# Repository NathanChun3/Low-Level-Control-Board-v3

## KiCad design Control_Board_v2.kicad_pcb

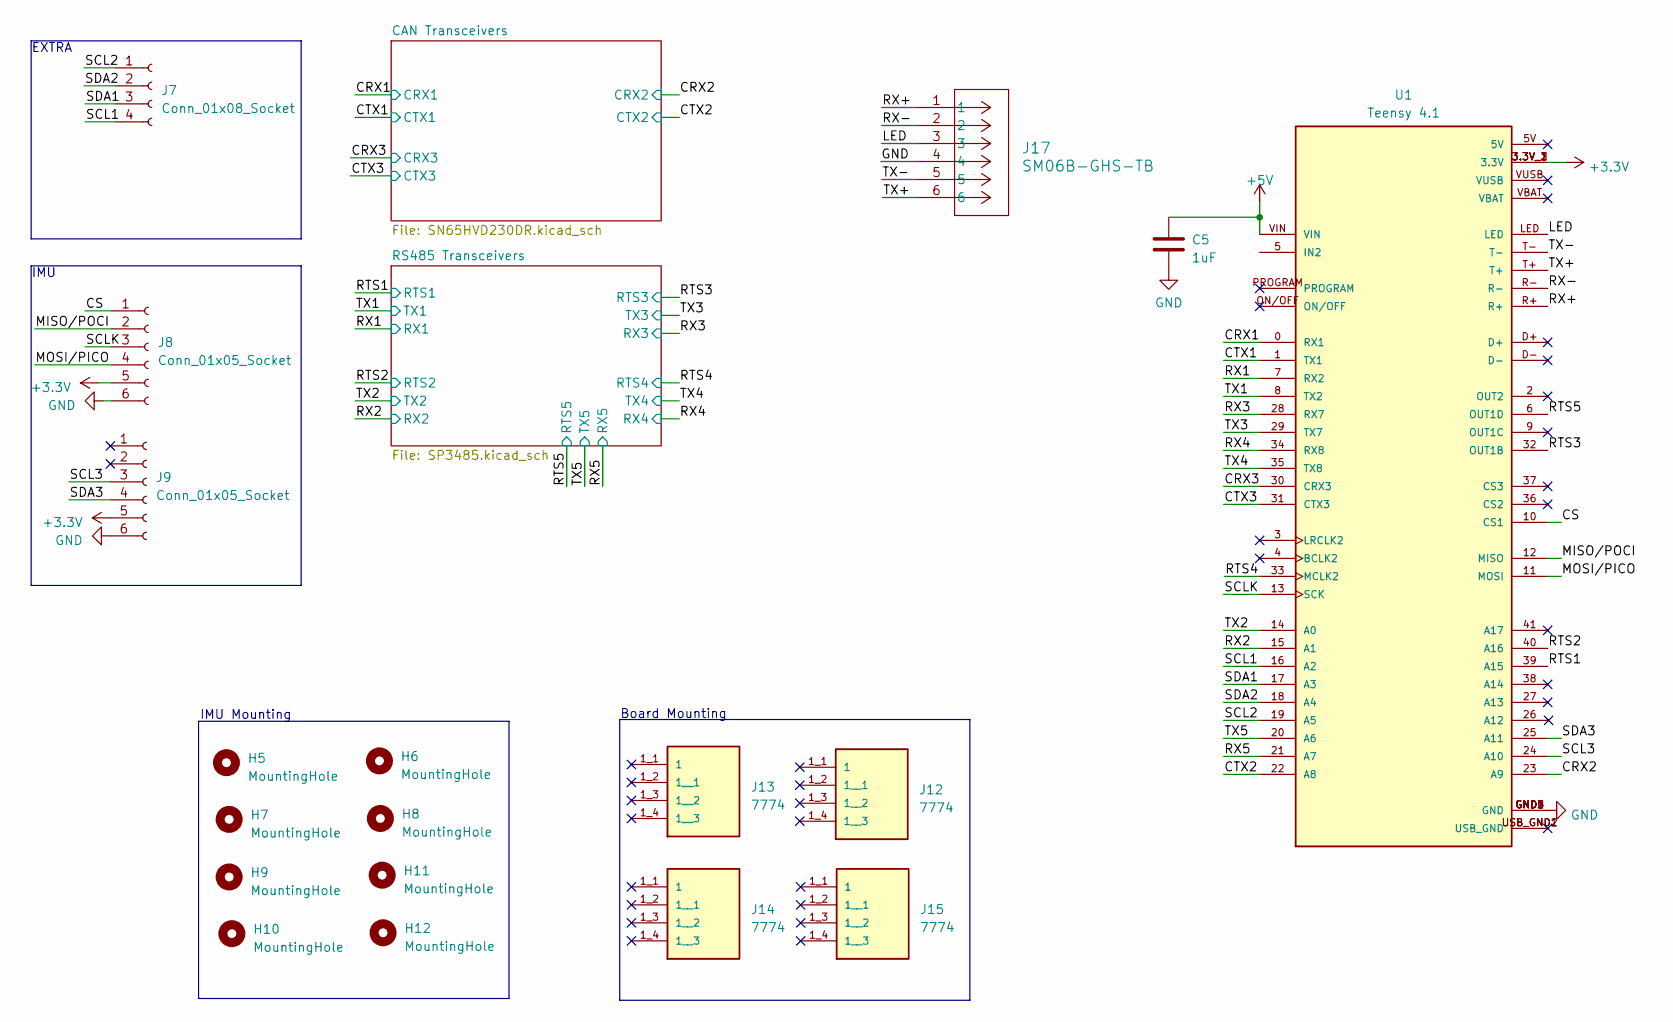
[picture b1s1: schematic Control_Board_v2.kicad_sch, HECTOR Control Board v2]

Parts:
C5: 1uF; C_1206_3216Metric
H5, H6, H7, H8, H9, H10, H11, H12: MountingHole; MountingHole_2.7mm_M2.5
J7: Conn_01x08_Socket; PinHeader_1x04_P2.54mm_Vertical
J8, J9: Conn_01x05_Socket; PinHeader_1x06_P2.54mm_Vertical
J12, J13, J14, J15: 7774; KEYSTONE_7774; PARTREV 1.29.09
J17: SM06B-GHS-TB; CONN_SM06B-GHS-TB_JST
U1: Teensy 4.1; Teensy_4.1; PARTREV 4.1

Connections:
+3.3V: J8.5, J9.5, U1.3.3V_1 (3.3V), U1.3.3V_2 (3.3V), U1.3.3V_3 (3.3V); also elsewhere on the board
+5V: C5.1, U1.VIN; also elsewhere on the board
/CRX1: U1.0 (RX1); also elsewhere on the board
/CRX2: U1.23 (A9); also elsewhere on the board
/CRX3: U1.30 (CRX3); also elsewhere on the board
/CS: J8.1, U1.10 (CS1)
/CTX1: U1.1 (TX1); also elsewhere on the board
/CTX2: U1.22 (A8); also elsewhere on the board
/CTX3: U1.31 (CTX3); also elsewhere on the board
/LED: J17.3, U1.LED
/MISO/POCI: J8.2, U1.12 (MISO)
/MOSI/PICO: J8.4, U1.11 (MOSI)
/RTS1: U1.39 (A15); also elsewhere on the board
/RTS2: U1.40 (A16); also elsewhere on the board
/RTS3: U1.32 (OUT1B); also elsewhere on the board
/RTS4: U1.33 (MCLK2); also elsewhere on the board
/RTS5: U1.6 (OUT1D); also elsewhere on the board
/RX1: U1.7 (RX2); also elsewhere on the board
/RX2: U1.15 (A1); also elsewhere on the board
/RX3: U1.28 (RX7); also elsewhere on the board
/RX4: U1.34 (RX8); also elsewhere on the board
/RX5: U1.21 (A7); also elsewhere on the board
/RX+: J17.1, U1.R+
/RX-: J17.2, U1.R-
/SCL1: J7.4, U1.16 (A2)
/SCL2: J7.1, U1.19 (A5)
/SCL3: J9.3, U1.24 (A10)
/SCLK: J8.3, U1.13 (SCK)
/SDA1: J7.3, U1.17 (A3)
/SDA2: J7.2, U1.18 (A4)
/SDA3: J9.4, U1.25 (A11)
/TX1: U1.8 (TX2); also elsewhere on the board
/TX2: U1.14 (A0); also elsewhere on the board
/TX3: U1.29 (TX7); also elsewhere on the board
/TX4: U1.35 (TX8); also elsewhere on the board
/TX5: U1.20 (A6); also elsewhere on the board
/TX+: J17.6, U1.T+
/TX-: J17.5, U1.T-
GND: C5.2, J8.6, J9.6, J17.4, U1.GND1 (GND), U1.GND2 (GND), U1.GND3 (GND), U1.GND4 (GND), U1.GND5 (GND); also elsewhere on the board

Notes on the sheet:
IMU
IMU Mounting
Board Mounting
EXTRA

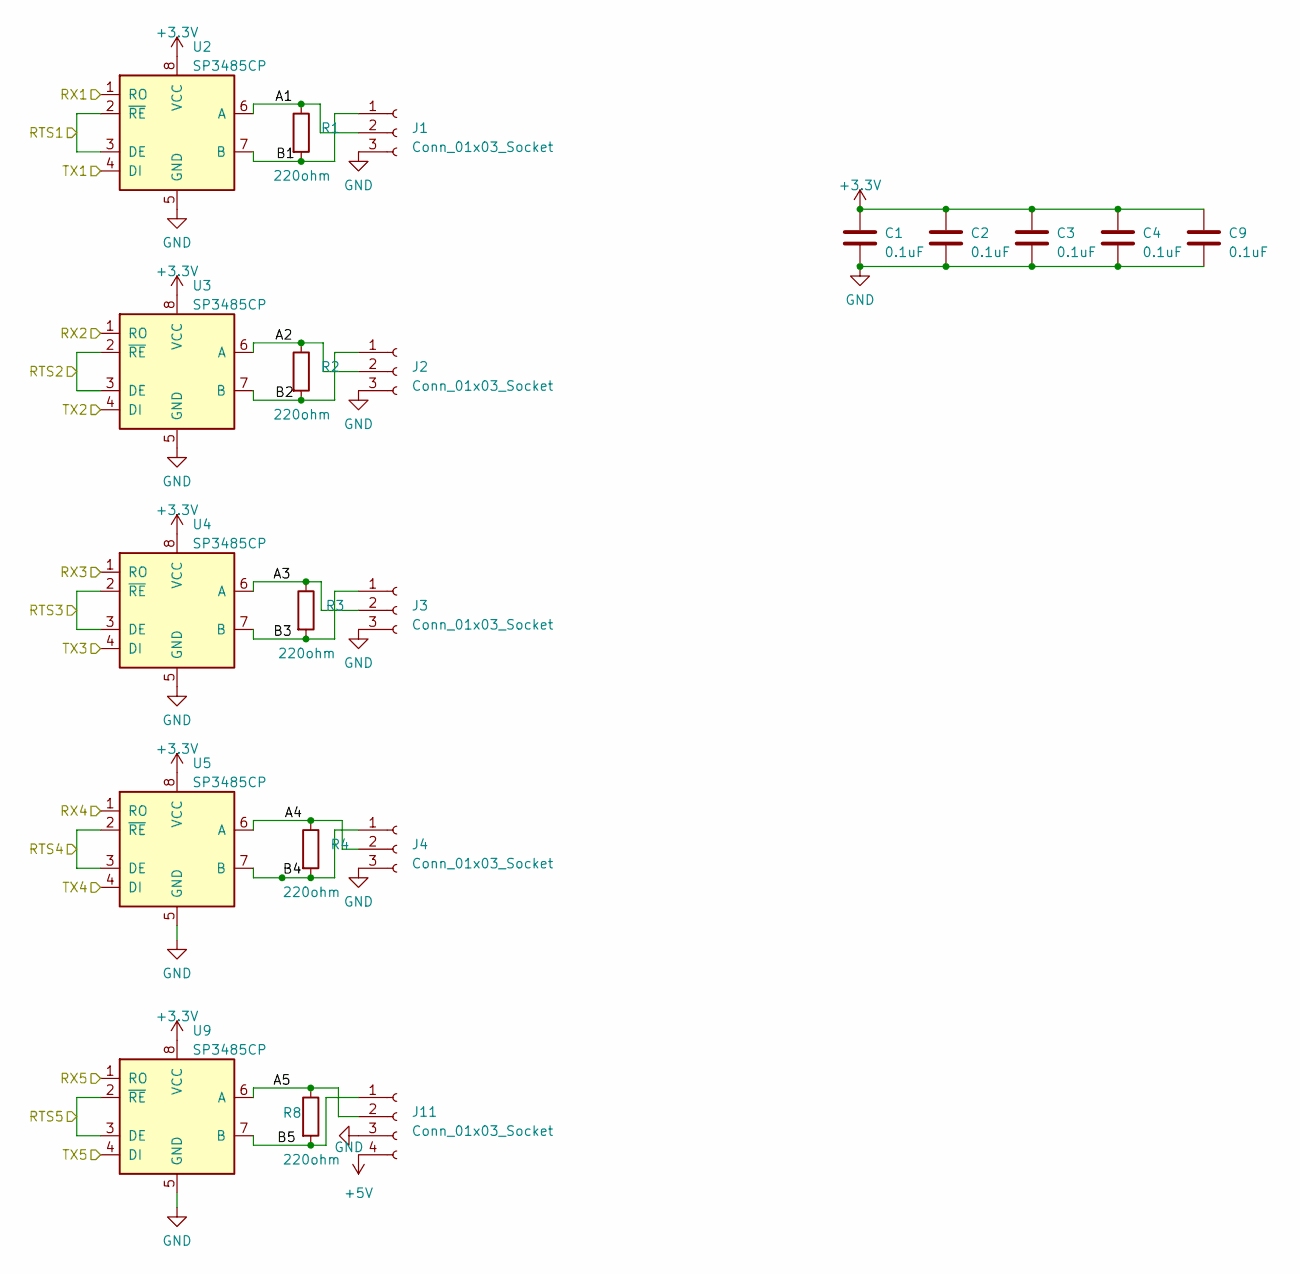
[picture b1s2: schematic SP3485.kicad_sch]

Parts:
C1, C2, C3, C4, C9: 0.1uF; C_1206_3216Metric
J1, J2, J3, J4: Conn_01x03_Socket; JST_GH_SM03B-GHS-TB_1x03-1MP_P1.25mm_Horizontal
J11: Conn_01x03_Socket; JST_GH_SM04B-GHS-TB_1x04-1MP_P1.25mm_Horizontal
R1, R2, R3, R4, R8: 220ohm; R_1206_3216Metric
U2, U3, U4, U5, U9: SP3485CP; SOIC-8_3.9x4.9mm_P1.27mm

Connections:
+3.3V: C1.1, C2.1, C3.1, C4.1, C9.1, U2.8 (VCC), U3.8 (VCC), U4.8 (VCC), U5.8 (VCC), U9.8 (VCC); also elsewhere on the board
+5V: J11.4; also elsewhere on the board
/RS485 Transceivers/A1: J1.2, R1.1, U2.6 (A)
/RS485 Transceivers/A2: J2.2, R2.1, U3.6 (A)
/RS485 Transceivers/A3: J3.2, R3.1, U4.6 (A)
/RS485 Transceivers/A4: J4.2, R4.1, U5.6 (A)
/RS485 Transceivers/A5: J11.2, R8.1, U9.6 (A)
/RS485 Transceivers/B1: J1.1, R1.2, U2.7 (B)
/RS485 Transceivers/B2: J2.1, R2.2, U3.7 (B)
/RS485 Transceivers/B3: J3.1, R3.2, U4.7 (B)
/RS485 Transceivers/B4: J4.1, R4.2, U5.7 (B)
/RS485 Transceivers/B5: J11.1, R8.2, U9.7 (B)
/RTS1: U2.2 (~RE), U2.3 (DE); also elsewhere on the board
/RTS2: U3.2 (~RE), U3.3 (DE); also elsewhere on the board
/RTS3: U4.2 (~RE), U4.3 (DE); also elsewhere on the board
/RTS4: U5.2 (~RE), U5.3 (DE); also elsewhere on the board
/RTS5: U9.2 (~RE), U9.3 (DE); also elsewhere on the board
/RX1: U2.1 (RO); also elsewhere on the board
/RX2: U3.1 (RO); also elsewhere on the board
/RX3: U4.1 (RO); also elsewhere on the board
/RX4: U5.1 (RO); also elsewhere on the board
/RX5: U9.1 (RO); also elsewhere on the board
/TX1: U2.4 (DI); also elsewhere on the board
/TX2: U3.4 (DI); also elsewhere on the board
/TX3: U4.4 (DI); also elsewhere on the board
/TX4: U5.4 (DI); also elsewhere on the board
/TX5: U9.4 (DI); also elsewhere on the board
GND: C1.2, C2.2, C3.2, C4.2, C9.2, J1.3, J2.3, J3.3, J4.3, J11.3, U2.5 (GND), U3.5 (GND), U4.5 (GND), U5.5 (GND), U9.5 (GND); also elsewhere on the board

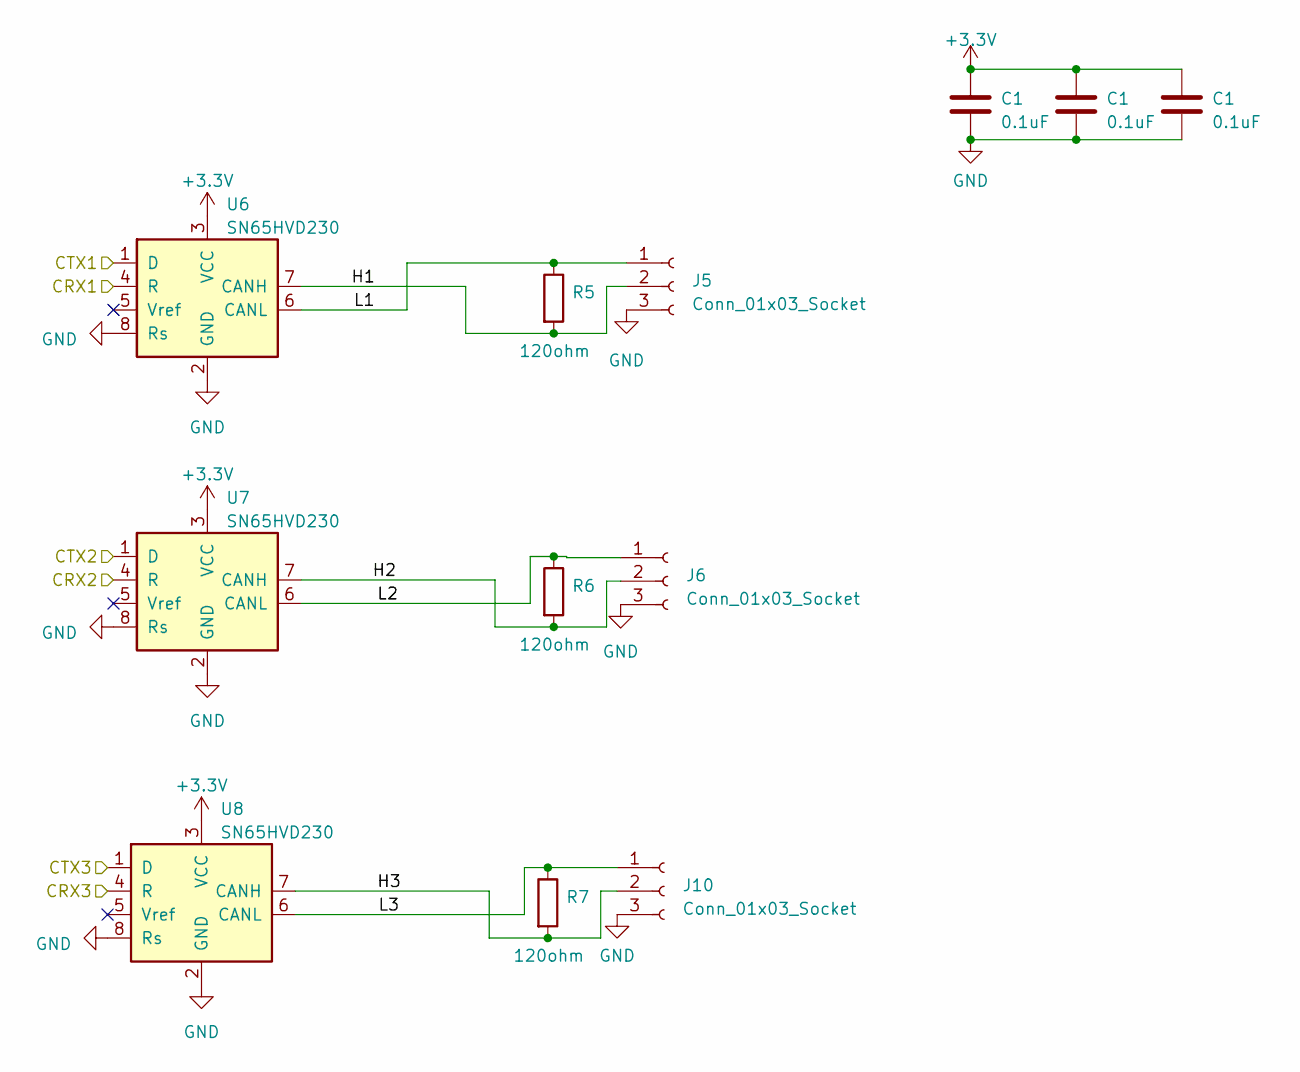
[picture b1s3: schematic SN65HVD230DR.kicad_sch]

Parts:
C1: 0.1uF; C_1206_3216Metric
J5, J6, J10: Conn_01x03_Socket; JST_GH_SM03B-GHS-TB_1x03-1MP_P1.25mm_Horizontal
R5, R6, R7: 120ohm; R_1206_3216Metric
U6, U7, U8: SN65HVD230; SOIC-8_3.9x4.9mm_P1.27mm

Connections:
+3.3V: C1.1, U6.3 (VCC), U7.3 (VCC), U8.3 (VCC); also elsewhere on the board
/CAN Transceivers/H1: J5.2, R5.2, U6.7 (CANH)
/CAN Transceivers/H2: J6.2, R6.2, U7.7 (CANH)
/CAN Transceivers/H3: J10.2, R7.2, U8.7 (CANH)
/CAN Transceivers/L1: J5.1, R5.1, U6.6 (CANL)
/CAN Transceivers/L2: J6.1, R6.1, U7.6 (CANL)
/CAN Transceivers/L3: J10.1, R7.1, U8.6 (CANL)
/CRX1: U6.4 (R); also elsewhere on the board
/CRX2: U7.4 (R); also elsewhere on the board
/CRX3: U8.4 (R); also elsewhere on the board
/CTX1: U6.1 (D); also elsewhere on the board
/CTX2: U7.1 (D); also elsewhere on the board
/CTX3: U8.1 (D); also elsewhere on the board
GND: C1.2, J5.3, J6.3, J10.3, U6.2 (GND), U6.8 (Rs), U7.2 (GND), U7.8 (Rs), U8.2 (GND), U8.8 (Rs); also elsewhere on the board

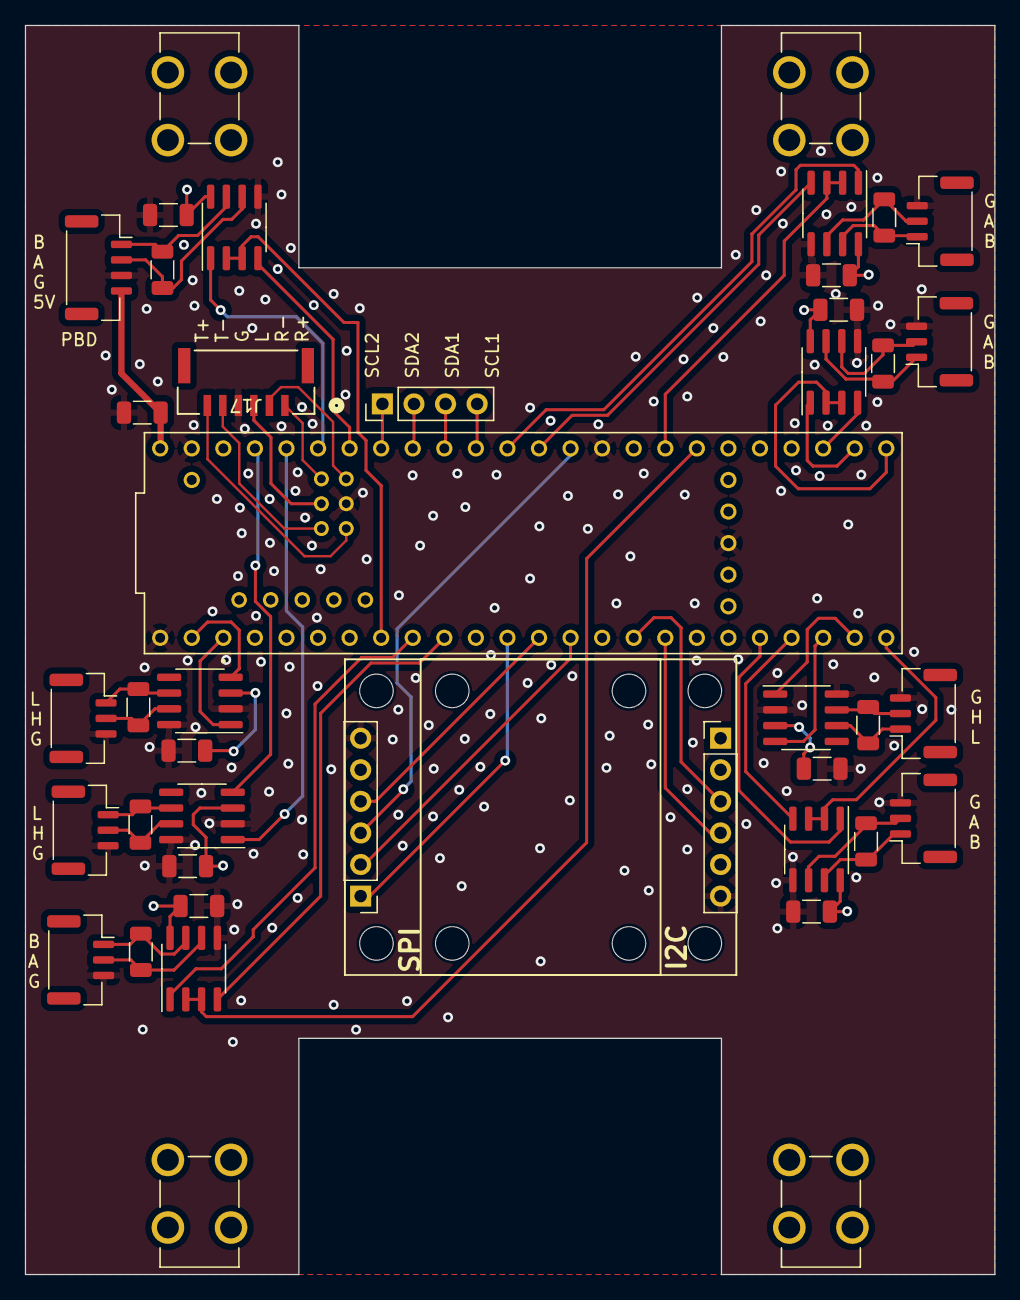
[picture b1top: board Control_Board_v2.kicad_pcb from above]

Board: 4 copper layers, 78.0 x 100.5 mm, 50 parts (0 on the bottom side), 55 nets.

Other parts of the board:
C6, C7, C8: 0.1uF; C_1206_3216Metric

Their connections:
+3.3V: C6.1, C7.1, C8.1; also elsewhere on the board
GND: C6.2, C7.2, C8.2; also elsewhere on the board
